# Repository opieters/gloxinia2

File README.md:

# gloxinia2

This is the second version of [Gloxinia](https://github.com/opieters/gloxinia), a research-focussed measurement platform that is tailored for deployment in greenhouses. Its goals are simple interconnectivity, flexbibility and cost-effectiveness.

## Architecture

The general architecture from the inital version remained, but some boards are not separate noted in place of add-on components. At it's core, the system comprises of a set of communicating nodes. Three possible options are:
- dicio: a node with serial interconnectivity, such that the system can interface with a computer. This node also features storage (16GB). This node can also send commands to other nodes in case of errors or crashes.
- sylvatica: a node with eight 16-bit ADCs
- planalta: a node with four LIAs (advanced analogue sensors)

All nodes communicate over a CAN bus and dicio nodes also have UART connection for communication computers. Plugging in a USB-C cable in the right port should suffice to connect to the system. Make sure to only plug cables to matching interfaces, since the hardware can be damaged otherwise. The interfaces are detailed in the PCB design and the interface section below. 

Note that the CAN bus requires termination. No automatic termination is implemented, so the use needs to manually terminate the CAN lines!

Each board interface also has an I2C port (not that some of the ports share the same physical interface), and analogue ports and a One Wire port. One Wire is currently not supported in the software. 

## Interfacing

Each node consists of a stack of boards. The base board with the analogue and digital processing, a botton connectivity board to interconnect different nodes and an optional top interfacing board (only for sylvatica).

### Dicio

Base board: [IF1] [IF2] [IF3] [IF4]
IF board: [Serial/USB] [] [CAN] [CAN]

### Sylvatica

Top board: [IF4] [IF5] [IF6] [IF7]
Base board: [IF1] [IF2] [IF3] [IF4]
IF board: [] [] [CAN] [CAN]

### Planalta

Base board: [IF1] [IF2] [IF3] [IF4]
IF board: [] [] [CAN] [CAN]

Note that IF1-4 are not feature-identical, IF1 supports a faster LIA (when others disabled) than IF2, 3 and 4 resp. See software implementation for details. These interfaces to no feature a 1W port.

## Software

The software consists of several parts: the embedded C code, the C++ GUI and the Python readout script. 

The embedded code is in the `firmware` folder. A separate MPLAB X project is created per hardware board (dicio, planalta and sylvatica). The code is written in C and compiled with the XC16 compiler. The code is written in a modular fashion, such that it is easy to add new features. The code is documented in the source files. Common files are included in the `lib2` folder. 

A bootloader project was also created to update the devices over CAN and UART, but this was not tested and should not yet be used in production. The UART version was slightly tested and first results were promising.

The GUI code is written in C++ using the Qt framework. A recent version of Qt 6 is necessary to build the project. Qt Designer files are included with in the `gui_qt` folder to get started with this project. 

## Enclousure

A 3D printable enclosure design is included in the `enclosure` folder, along with the STL files. The design is made in OpenSCAD.

A radiation shield was also designed for the environemental sensors, which is included in the

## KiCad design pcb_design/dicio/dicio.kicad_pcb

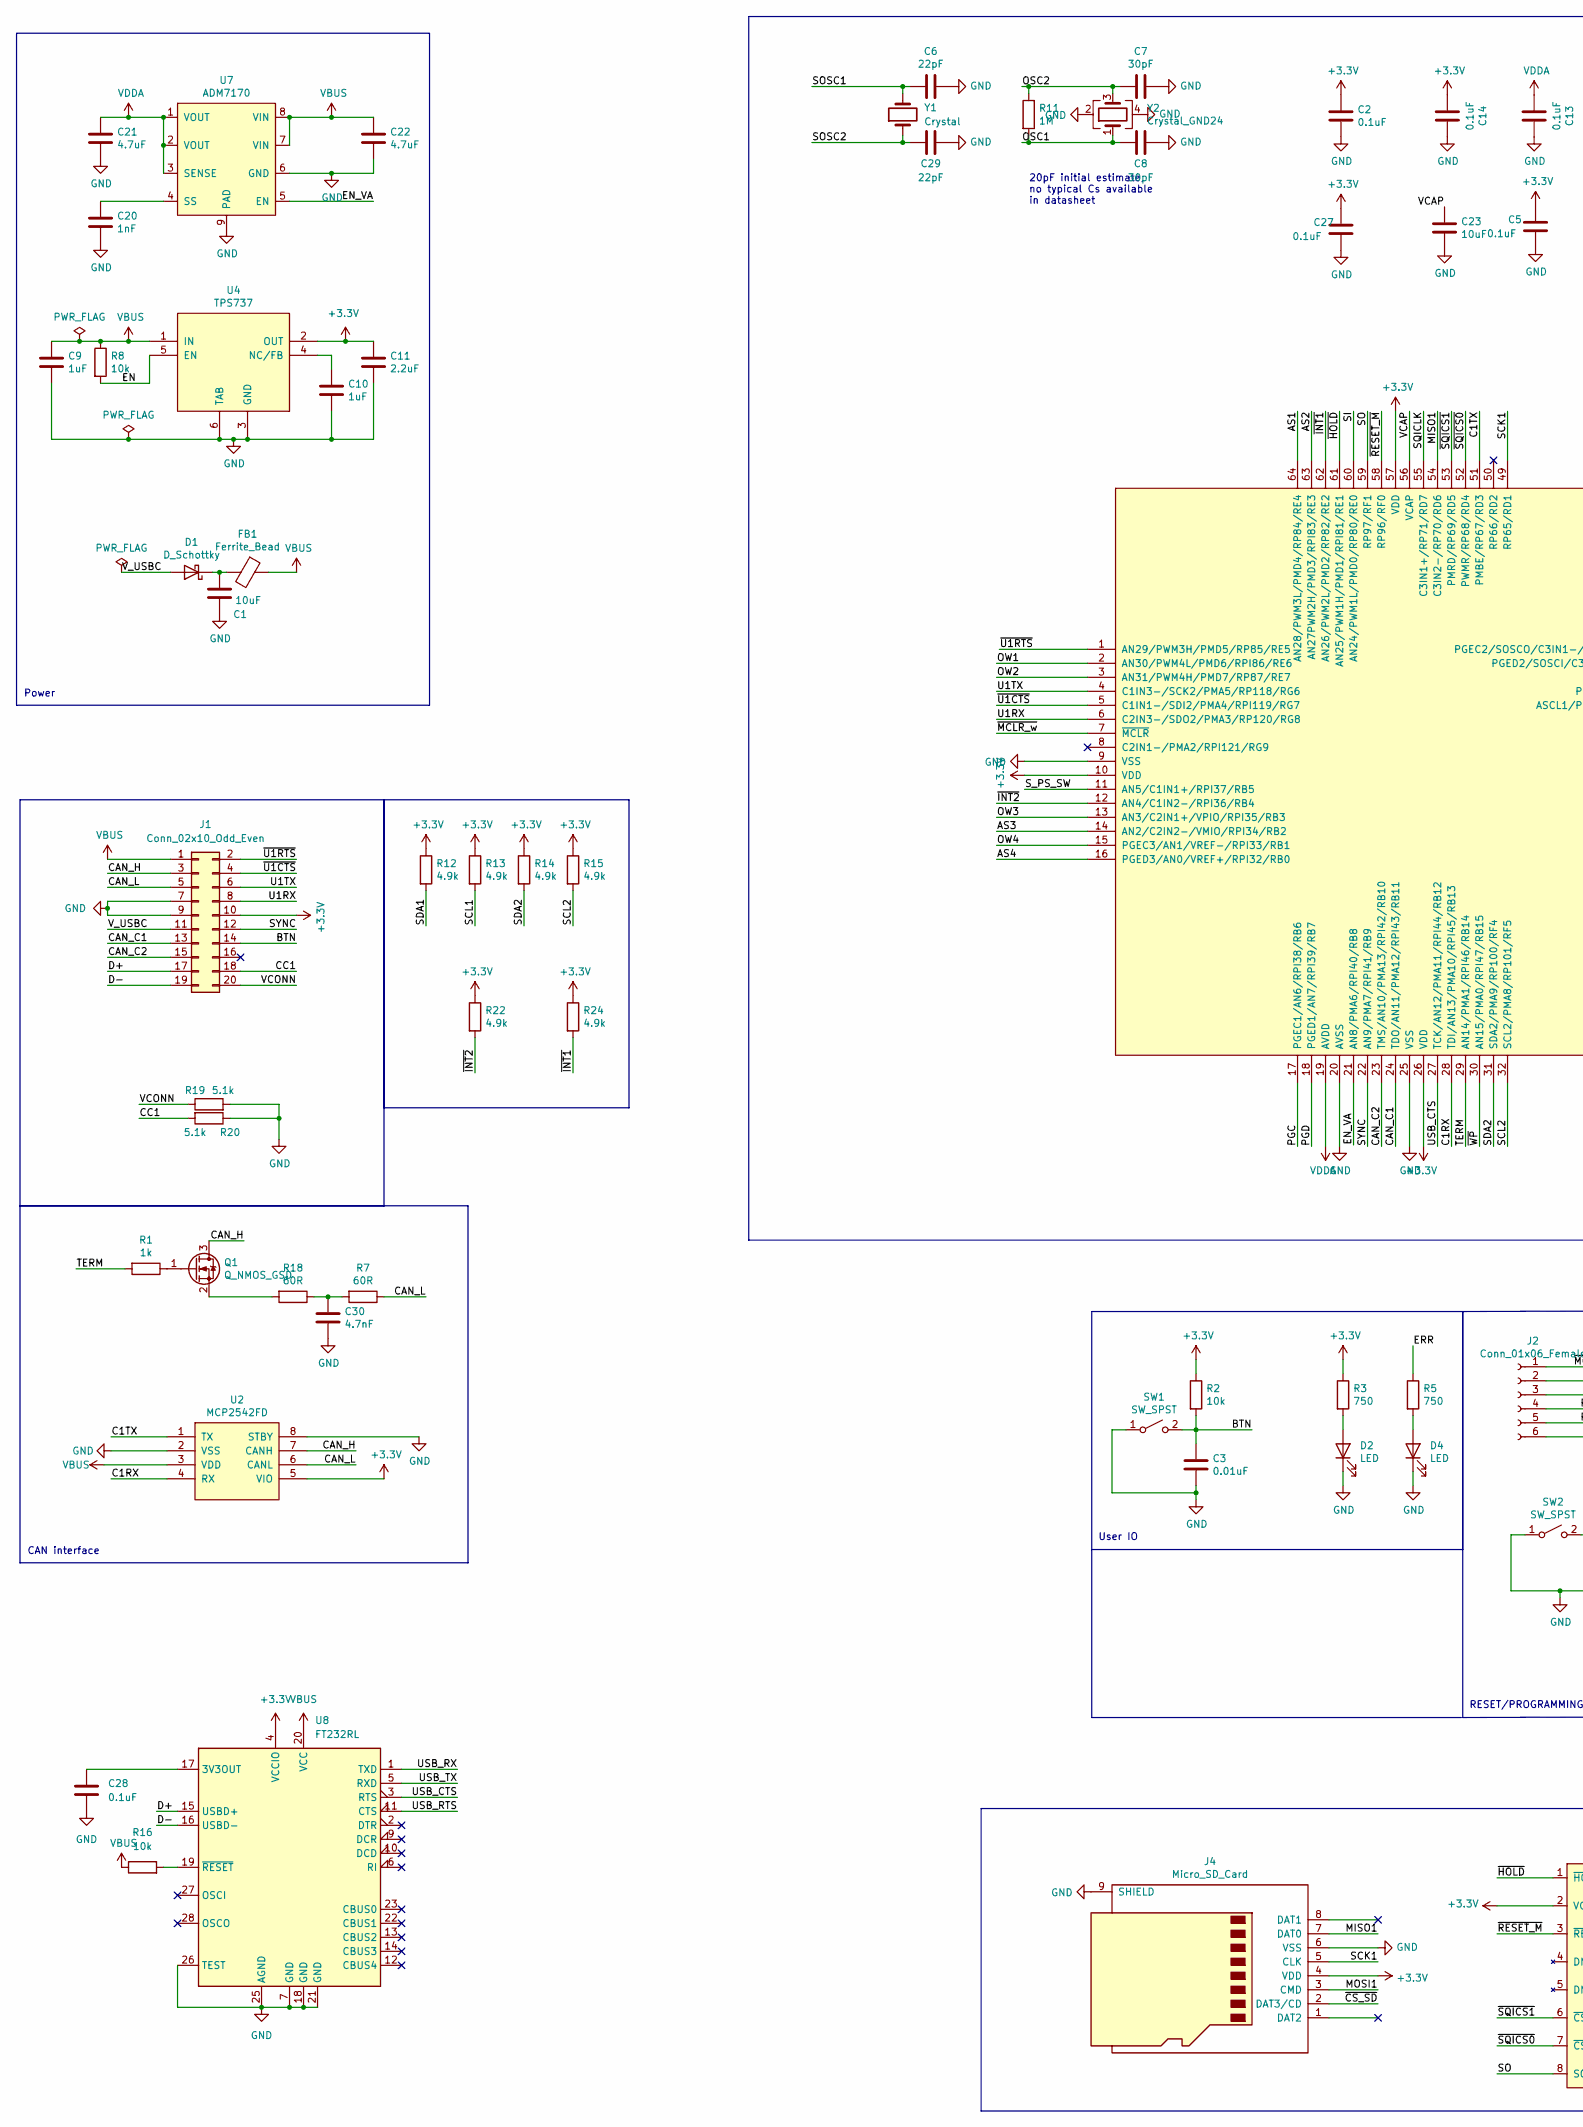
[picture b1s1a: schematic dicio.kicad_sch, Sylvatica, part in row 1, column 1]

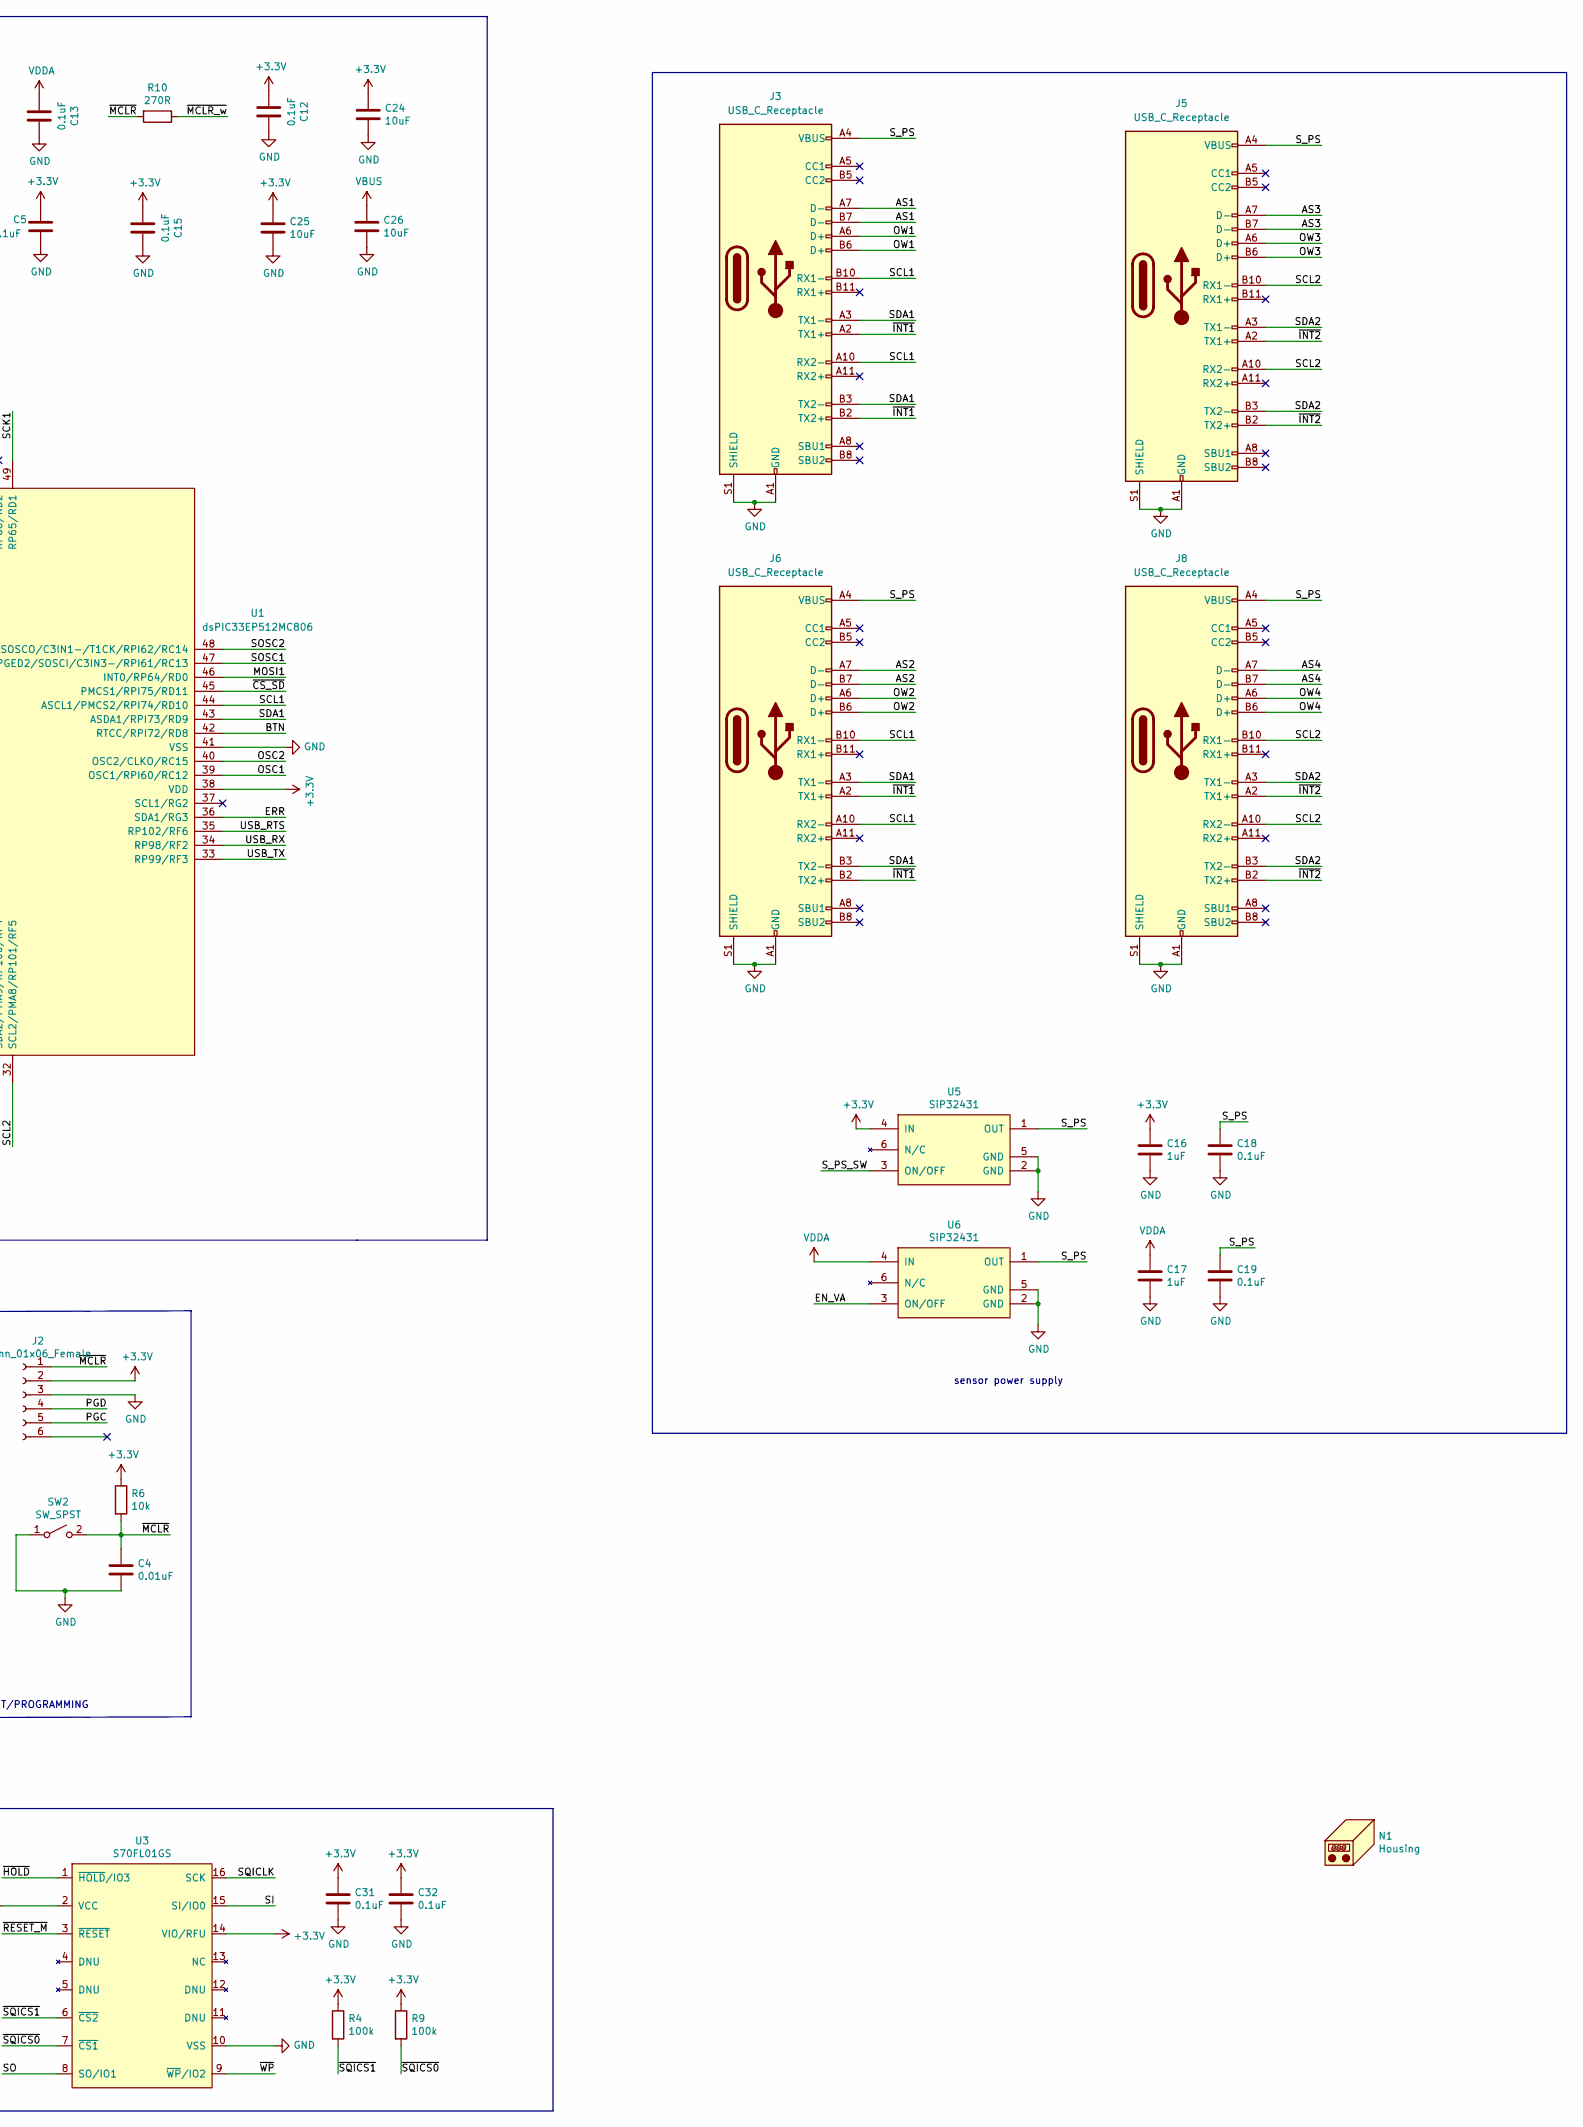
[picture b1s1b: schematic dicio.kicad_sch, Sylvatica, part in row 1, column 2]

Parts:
C1, C24, C25, C26: 10uF; C_1210_3225Metric; Mouser 963-TMK325BJ106KM-P
C2, C5, C12, C13, C14, C15, C27: 0.1uF; C_0603_1608Metric; Mouser 710-885012206071
C3, C4: 0.01uF; C_0603_1608Metric; Mouser 710-885012206065
C6, C29: 22pF; C_0603_1608Metric; Mouser 80-C0603C220J3HACTU
C7, C8: 30pF; C_0603_1608Metric; Mouser 80-C0603C300G1HACTU
C9, C10: 1uF; C_0603_1608Metric; Mouser 963-TMK325B7105KD-T
C11: 2.2uF; C_1206_3216Metric; Mouser 791-1206X225K250CT
C16, C17: 1uF; C_0603_1608Metric
C18, C19, C28, C31, C32: 0.1uF; C_0603_1608Metric
C20: 1nF; C_0603_1608Metric
C21, C22: 4.7uF; C_1206_3216Metric; Mouser 80-C1206C475K4PAC
C23: 10uF; C_1210_3225Metric
C30: 4.7nF; C_0603_1608Metric
D1: D_Schottky; D_SMB; Mouser 621-B340LB-F
D2, D4: LED; LED_0603_1608Metric; Mouser 78-TLMS1000
FB1: Ferrite_Bead; L_0805_2012Metric; Mouser 875-MI0805K400R-10
J1: Conn_02x10_Odd_Even; SAMTEC_TMMH-110-01-T-DV
J2: Conn_01x06_Female; PinSocket_1x06_P2.54mm_Vertical
J3, J5, J6, J8: USB_C_Receptacle; USB_C_Receptacle_Amphenol_12401861XX12A; Mouser 523-124018612112A
J4: Micro_SD_Card; microSD_HC_Wuerth_693072010801
N1: Housing; Enclosure-Gloxinia4; Mouser 546-1554LA2GYCL
Q1: Q_NMOS_GSD; SOT-23; Mouser 771-PMV20XNER
R1: 1k; R_0603_1608Metric
R2, R6, R8: 10k; R_0603_1608Metric; Mouser 284-APC0603B10K0N
R3, R5: 750; R_0603_1608Metric; Mouser 603-RC0603FR-07750RL
R4, R9: 100k; R_0603_1608Metric
R7, R18: 60R; R_0603_1608Metric; Mouser 594-5063JD120R0F
R10: 270R; R_0603_1608Metric; Mouser 603-RC0603FR-07270RL
R11: 1M; R_0603_1608Metric
R12, R13, R14, R15, R22, R24: 4.9k; R_0603_1608Metric; Mouser 603-RC0603FR-0724K9L
R16: 10k; R_0603_1608Metric
R19, R20: 5.1k; R_0603_1608Metric; Mouser 603-AC0603FR-135K1L
SW1, SW2: SW_SPST; SW_Push_1P1T_NO_CK_KMR2; Mouser 611-KMR621NGLFS
U1: dsPIC33EP512MC806; TQFP-64_10x10mm_P0.5mm
U2: MCP2542FD; SOIC-8_3.9x4.9mm_P1.27mm; Mouser 579-MCP2542FDT-E/SN
U3: S70FL01GS; SOIC-16_25.75x18.75mm_P2.5mm
U4: TPS737; SOT-223-6; Mouser 595-TPS73733DCQR
U5, U6: SiP32431; SOT-363_SC-70-6
U7: ADM7170; LFCSP-8-1EP_3x3mm_P0.5mm_EP1.45x1.74mm
U8: FT232RL; SSOP-28_5.3x10.2mm_P0.65mm
Y1: Crystal; Crystal_SMD_3215-2Pin_3.2x1.5mm; Mouser 520-.327-9-34QCNT
Y2: Crystal_GND24; Crystal_SMD_Abracon_ABM3B-4Pin_5.0x3.2mm; Mouser 520-80-10-30B-CWNT

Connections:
+3.3V: C2.1, C5.1, C11.1, C12.2, C14.2, C15.1, C16.1, C24.1, C25.1, C27.1, C31.1, C32.1, J1.10, J2.2, J4.4 (VDD), R2.1, R3.1, R4.1, R6.1, R9.1, R12.1, R13.1, R14.1, R15.1, R22.1, R24.1, U1.10 (VDD), U1.26 (VDD), U1.38 (VDD), U1.57 (VDD), U2.5 (VIO), U3.2 (VCC), U3.14 (VIO/RFU), U4.2 (OUT), U5.4 (IN), U8.4 (VCCIO)
/AS1: J3.A7 (D-), J3.B7 (D-), U1.64 (AN28/PWM3L/PMD4/RP84/RE4)
/AS2: J6.A7 (D-), J6.B7 (D-), U1.63 (AN27PWM2H/PMD3/RPI83/RE3)
/AS3: J5.A7 (D-), J5.B7 (D-), U1.14 (AN2/C2IN2-/VMIO/RPI34/RB2)
/AS4: J8.A7 (D-), J8.B7 (D-), U1.16 (PGED3/AN0/VREF+/RPI32/RB0)
/BTN: C3.1, J1.14, R2.2, SW1.2 (B), U1.42 (RTCC/RPI72/RD8)
/C1RX: U1.28 (TDI/AN13/PMA10/RPI45/RB13), U2.4 (RX)
/C1TX: U1.51 (PMBE/RP67/RD3), U2.1 (TX)
/CAN_C1: J1.13, U1.24 (TDO/AN11/PMA12/RPI43/RB11)
/CAN_C2: J1.15, U1.23 (TMS/AN10/PMA13/RPI42/RB10)
/CAN_H: J1.3, Q1.3 (D), U2.7 (CANH)
/CAN_L: J1.5, R7.1, U2.6 (CANL)
/CC1: J1.18, R20.2
/D+: J1.17, U8.15 (USBD+)
/D-: J1.19, U8.16 (USBD-)
/EN: R8.2, U4.5 (EN)
/EN_VA: U1.21 (AN8/PMA6/RPI40/RB8), U6.3 (ON/OFF), U7.5 (EN)
/ERR: R5.1, U1.36 (SDA1/RG3)
/MISO1: J4.7 (DAT0), U1.54 (C3IN2-/RP70/RD6)
/MOSI1: J4.3 (CMD), U1.46 (INT0/RP64/RD0)
/OSC1: C8.2, R11.2, U1.39 (OSC1/RPI60/RC12), Y2.1
/OSC2: C7.2, R11.1, U1.40 (OSC2/CLKO/RC15), Y2.3
/OW1: J3.A6 (D+), J3.B6 (D+), U1.2 (AN30/PWM4L/PMD6/RPI86/RE6)
/OW2: J6.A6 (D+), J6.B6 (D+), U1.3 (AN31/PWM4H/PMD7/RP87/RE7)
/OW3: J5.A6 (D+), J5.B6 (D+), U1.13 (AN3/C2IN1+/VPIO/RPI35/RB3)
/OW4: J8.A6 (D+), J8.B6 (D+), U1.15 (PGEC3/AN1/VREF-/RPI33/RB1)
/PGC: J2.5, U1.17 (PGEC1/AN6/RPI38/RB6)
/PGD: J2.4, U1.18 (PGED1/AN7/RPI39/RB7)
/SCK1: J4.5 (CLK), U1.49 (RP65/RD1)
/SCL1: J3.A10 (RX2-), J3.B10 (RX1-), J6.A10 (RX2-), J6.B10 (RX1-), R13.2, U1.44 (ASCL1/PMCS2/RPI74/RD10)
/SCL2: J5.A10 (RX2-), J5.B10 (RX1-), J8.A10 (RX2-), J8.B10 (RX1-), R15.2, U1.32 (SCL2/PMA8/RP101/RF5)
/SDA1: J3.A3 (TX1-), J3.B3 (TX2-), J6.A3 (TX1-), J6.B3 (TX2-), R12.2, U1.43 (ASDA1/RPI73/RD9)
/SDA2: J5.A3 (TX1-), J5.B3 (TX2-), J8.A3 (TX1-), J8.B3 (TX2-), R14.2, U1.31 (SDA2/PMA9/RP100/RF4)
/SI: U1.60 (AN24/PWM1L/PMD0/RP80/RE0), U3.15 (SI/IO0)
/SO: U1.59 (RP97/RF1), U3.8 (SO/IO1)
/SOSC1: C6.2, U1.47 (PGED2/SOSCI/C3IN3-/RPI61/RC13), Y1.2
/SOSC2: C29.2, U1.48 (PGEC2/SOSCO/C3IN1-/T1CK/RPI62/RC14), Y1.1
/SQICLK: U1.55 (C3IN1+/RP71/RD7), U3.16 (SCK)
/SYNC: J1.12, U1.22 (AN9/PMA7/RPI41/RB9)
/S_PS: C18.1, C19.1, J3.A4 (VBUS), J3.A9 (VBUS), J3.B4 (VBUS), J3.B9 (VBUS), J5.A4 (VBUS), J5.A9 (VBUS), J5.B4 (VBUS), J5.B9 (VBUS), J6.A4 (VBUS), J6.A9 (VBUS), J6.B4 (VBUS), J6.B9 (VBUS), J8.A4 (VBUS), J8.A9 (VBUS), J8.B4 (VBUS), J8.B9 (VBUS), U5.1 (OUT), U6.1 (OUT)
/S_PS_SW: U1.11 (AN5/C1IN1+/RPI37/RB5), U5.3 (ON/OFF)
/TERM: R1.2, U1.29 (AN14/PMA1/RPI46/RB14)
/U1RX: J1.8, U1.6 (C2IN3-/SDO2/PMA3/RP120/RG8)
/U1TX: J1.6, U1.4 (C1IN3-/SCK2/PMA5/RP118/RG6)
/USB_CTS: U1.27 (TCK/AN12/PMA11/RPI44/RB12), U8.3 (RTS)
/USB_RTS: U1.35 (RP102/RF6), U8.11 (CTS)
/USB_RX: U1.34 (RP98/RF2), U8.1 (TXD)
/USB_TX: U1.33 (RP99/RF3), U8.5 (RXD)
/VCAP: C23.1, U1.56 (VCAP)
/VCONN: J1.20, R19.1
/V_USBC: D1.2 (A), J1.11
/~CS_SD: J4.2 (DAT3/CD), U1.45 (PMCS1/RPI75/RD11)
/~HOLD: U1.61 (AN25/PWM1H/PMD1/RPI81/RE1), U3.1 (~HOLD/IO3)
/~INT1: J3.A2 (TX1+), J3.B2 (TX2+), J6.A2 (TX1+), J6.B2 (TX2+), R24.2, U1.62 (AN26/PWM2L/PMD2/RP82/RE2)
/~INT2: J5.A2 (TX1+), J5.B2 (TX2+), J8.A2 (TX1+), J8.B2 (TX2+), R22.2, U1.12 (AN4/C1IN2-/RPI36/RB4)
/~MCLR_w: R10.1, U1.7 (~MCLR)
/~MCLR: C4.1, J2.1, R6.2, R10.2, SW2.2 (B)
/~RESET_M: U1.58 (RP96/RF0), U3.3 (~RESET)
/~SQICS0: R9.2, U1.52 (PWMR/RP68/RD4), U3.7 (~CS1)
/~SQICS1: R4.2, U1.53 (PMRD/RP69/RD5), U3.6 (~CS2)
/~U1CTS: J1.4, U1.5 (C1IN1-/SDI2/PMA4/RPI119/RG7)
/~U1RTS: J1.2, U1.1 (AN29/PWM3H/PMD5/RP85/RE5)
/~WP: U1.30 (AN15/PMA0/RPI47/RB15), U3.9 (~WP/IO2)
GND: C1.2, C2.2, C3.2, C4.2, C5.2, C6.1, C7.1, C8.1, C9.2, C10.2, C11.2, C12.1, C13.1, C14.1, C15.2, C16.2, C17.2, C18.2, C19.2, C20.2, C21.2, C22.2, C23.2, C24.2, C25.2, C26.2, C27.2, C28.2, C29.1, C30.2, C31.2, C32.2, D2.1 (K), D4.1 (K), J1.7, J1.9, J2.3, J3.A1 (GND), J3.A12 (GND), J3.B1 (GND), J3.B12 (GND), J3.S1 (SHIELD), J4.6 (VSS), J4.9 (SHIELD), J5.A1 (GND), J5.A12 (GND), J5.B1 (GND), J5.B12 (GND), J5.S1 (SHIELD), J6.A1 (GND), J6.A12 (GND), J6.B1 (GND), J6.B12 (GND), J6.S1 (SHIELD), J8.A1 (GND), J8.A12 (GND), J8.B1 (GND), J8.B12 (GND), J8.S1 (SHIELD), R19.2, R20.1, SW1.1 (A), SW2.1 (A), U1.9 (VSS), U1.20 (AVSS), U1.25 (VSS), U1.41 (VSS), U2.2 (VSS), U2.8 (STBY), U3.10 (VSS), U4.3 (GND), U4.6 (TAB), U5.2 (GND), U5.5 (GND), U6.2 (GND), U6.5 (GND), U7.6 (GND), U7.9 (PAD), U8.7 (GND), U8.18 (GND), U8.21 (GND), U8.25 (AGND), U8.26 (TEST), Y2.2, Y2.4
unnamed: C1.1, D1.1 (K), FB1.2
unnamed: C10.1, U4.4 (NC/FB)
unnamed: C20.1, U7.4 (SS)
unnamed: C28.1, U8.17 (3V3OUT)
unnamed: C30.1, R7.2, R18.1
unnamed: D2.2 (A), R3.2
unnamed: D4.2 (A), R5.2
unnamed: Q1.1 (G), R1.1
unnamed: Q1.2 (S), R18.2
unnamed: R16.2, U8.19 (~RESET)
VBUS: C9.1, C22.1, C26.1, FB1.1, J1.1, R8.1, R16.1, U2.3 (VDD), U4.1 (IN), U7.7 (VIN), U7.8 (VIN), U8.20 (VCC)
VDDA: C13.2, C17.1, C21.1, U1.19 (AVDD), U6.4 (IN), U7.1 (VOUT), U7.2 (VOUT), U7.3 (SENSE)

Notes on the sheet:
sensor power supply
20pF initial estimate, no typical Cs available in datasheet
RESET/PROGRAMMING
CAN interface
User IO
Power

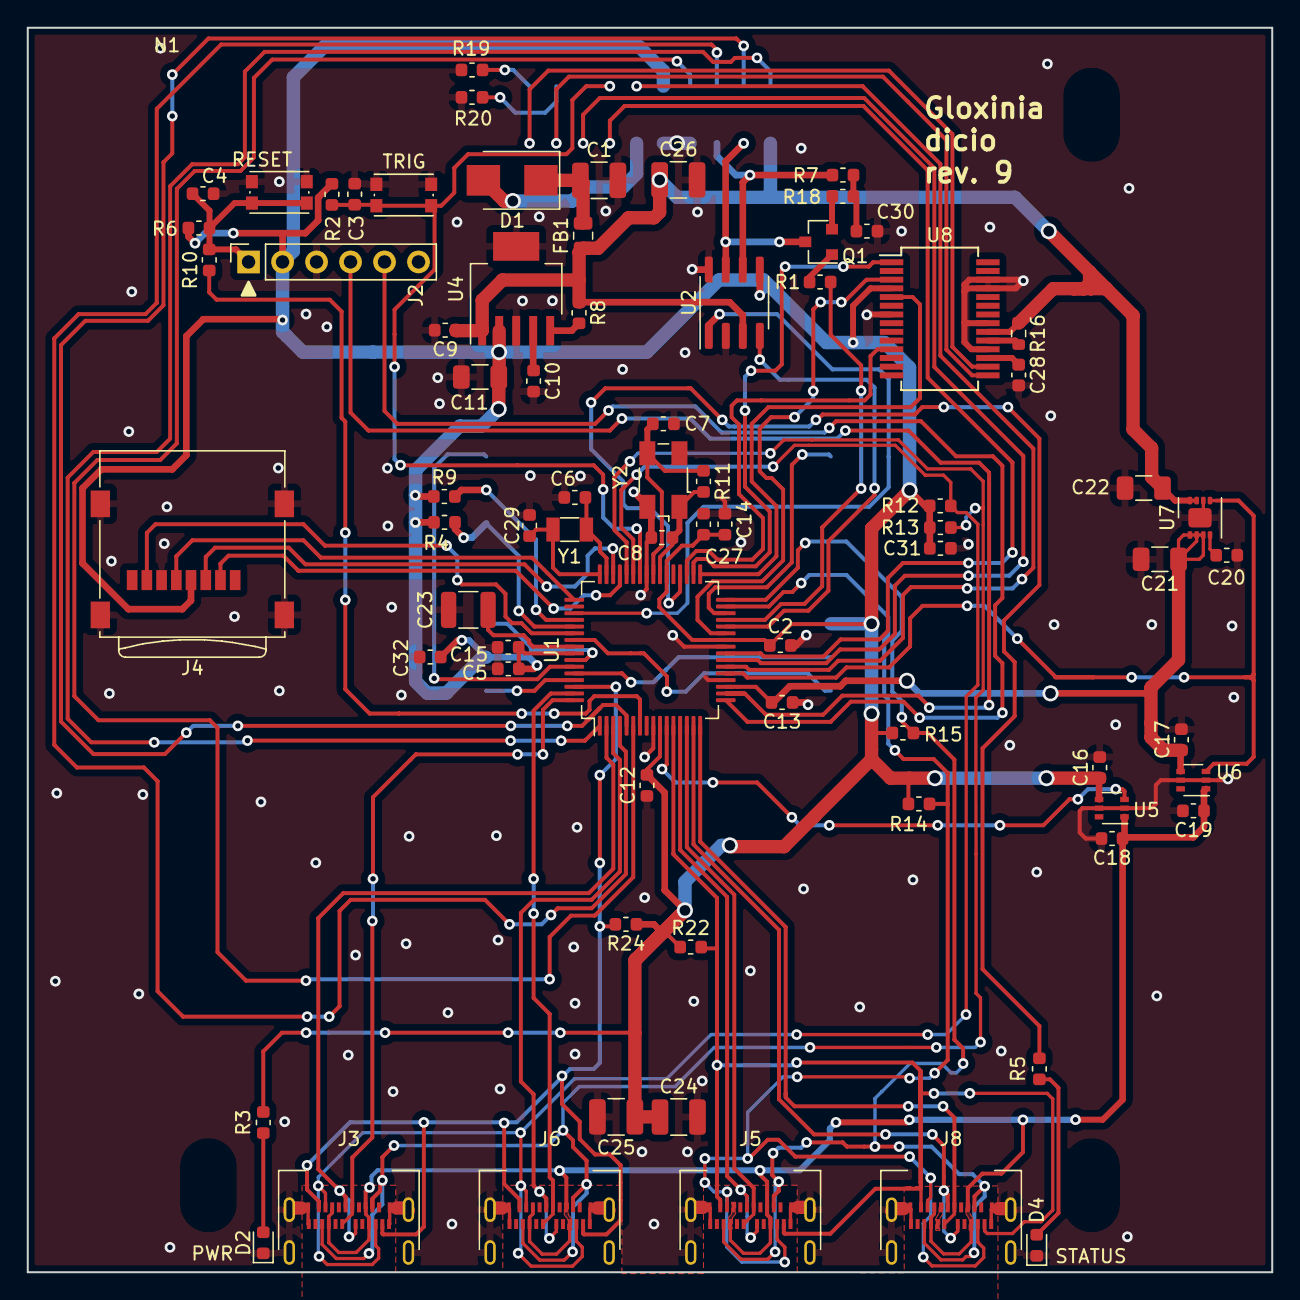
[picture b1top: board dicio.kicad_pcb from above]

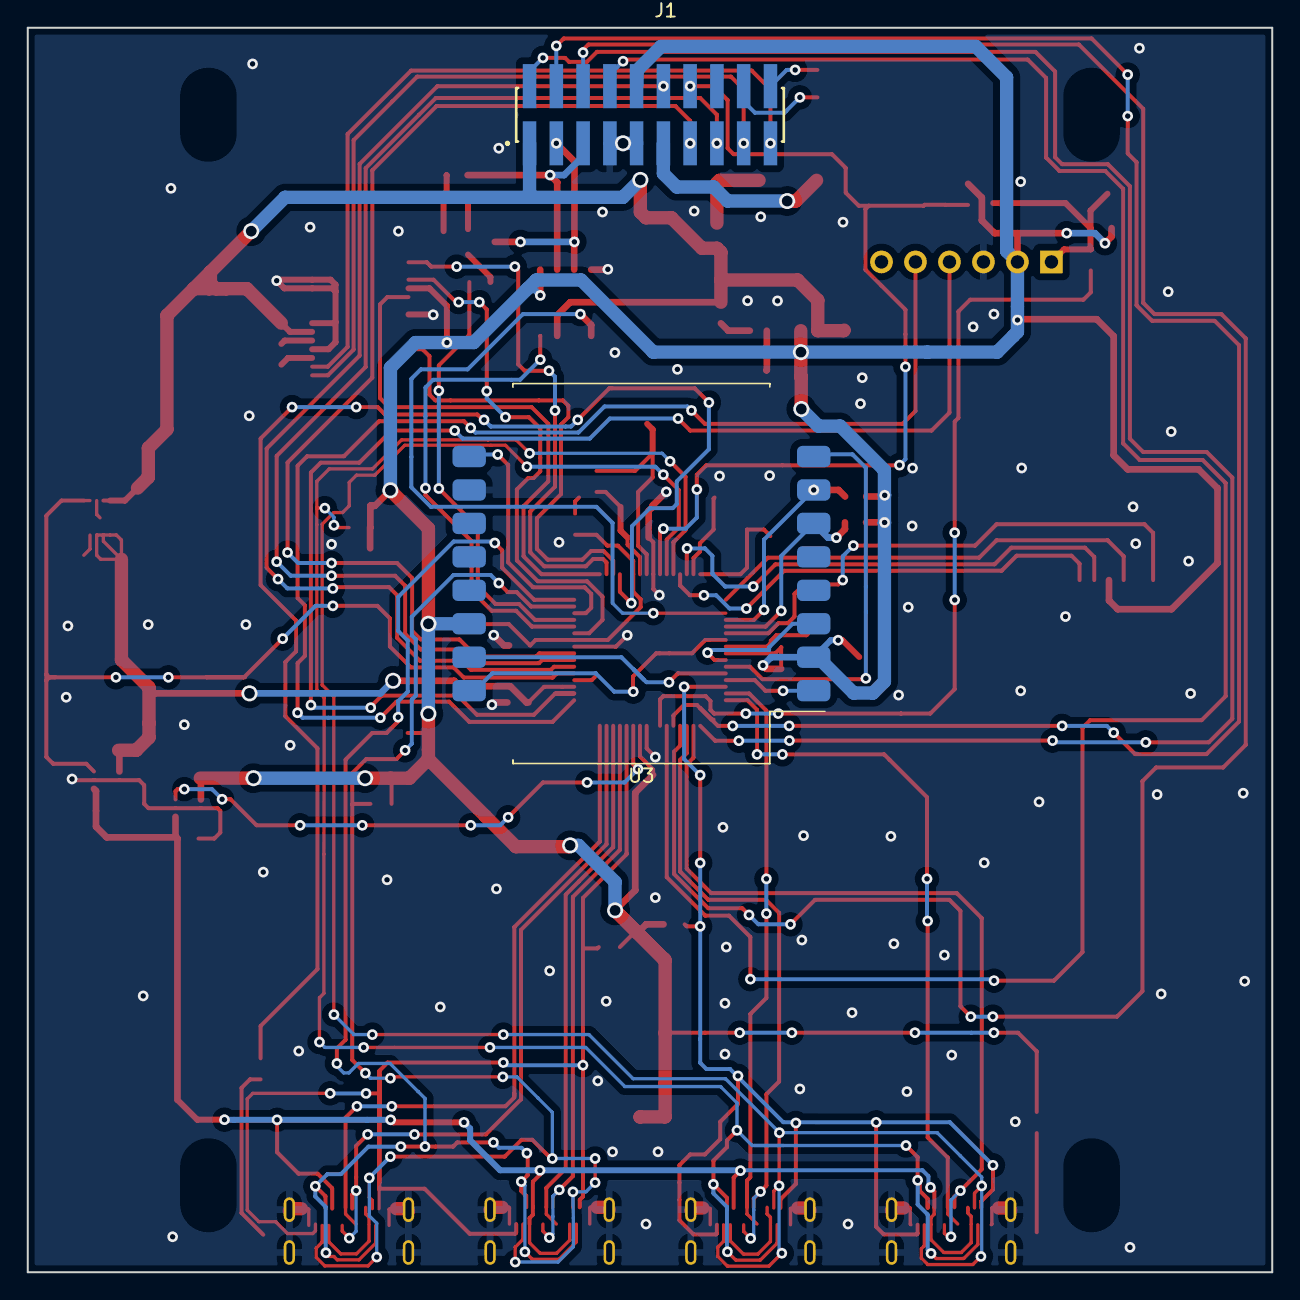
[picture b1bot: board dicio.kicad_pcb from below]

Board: 2 copper layers, 93.0 x 93.0 mm, 78 parts (2 on the bottom side), 76 nets.

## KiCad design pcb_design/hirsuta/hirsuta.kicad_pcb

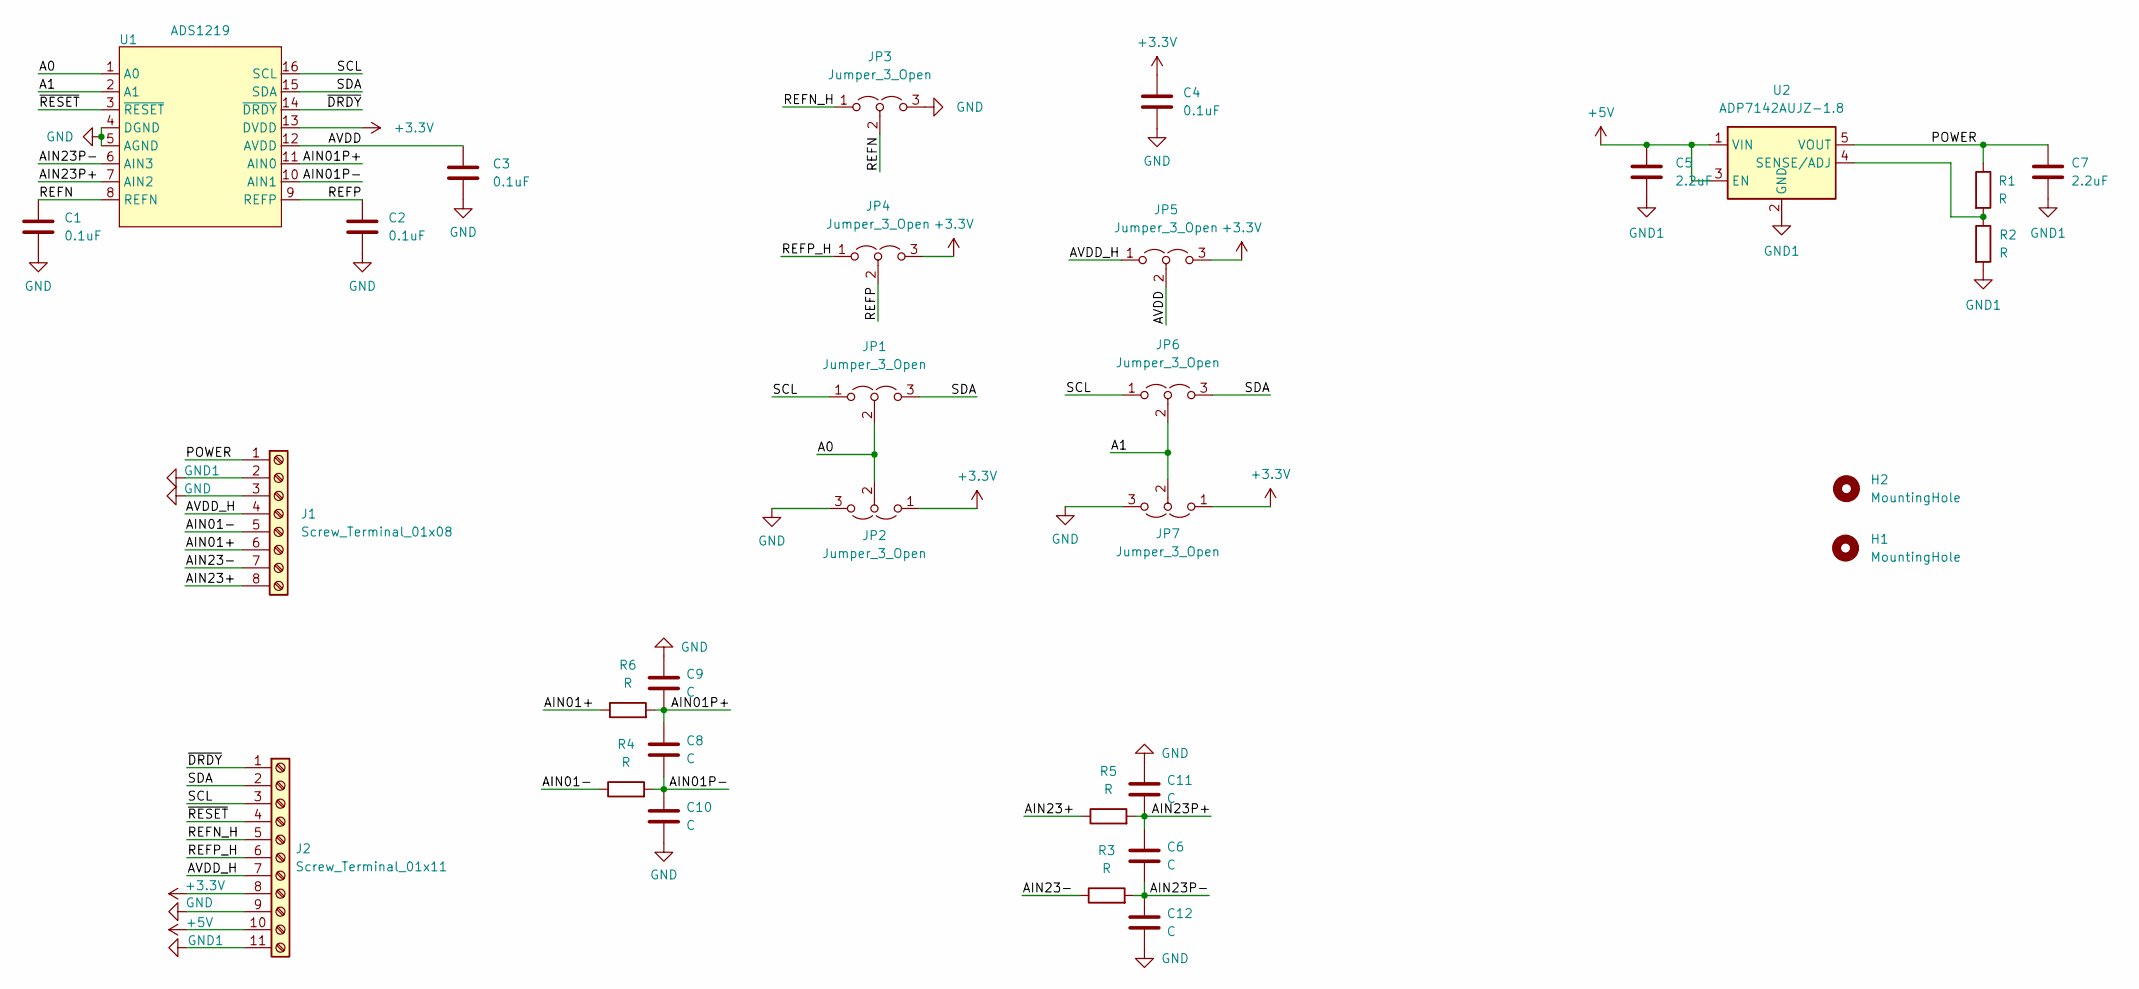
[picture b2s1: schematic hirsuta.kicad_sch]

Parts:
C1, C2, C3, C4: 0.1uF; C_0603_1608Metric
C5, C7: 2.2uF; C_1206_3216Metric
C6, C8, C9, C10, C11, C12: C; C_0603_1608Metric
H1, H2: MountingHole; MountingHole_3.2mm_M3
J1: Screw_Terminal_01x08; TerminalBlock_Phoenix_PT-1,5-8-3.5-H_1x08_P3.50mm_Horizontal
J2: Screw_Terminal_01x11; TerminalBlock_Phoenix_PT-1,5-11-3.5-H_1x11_P3.50mm_Horizont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
JP1, JP2, JP3, JP4, JP5, JP6, JP7: Jumper_3_Open; SolderJumper-3_P1.3mm_Open_Pad1.0x1.5mm
R1, R2, R3, R4, R5, R6: R; C_0603_1608Metric
U1: ADS1219; TSSOP-16-1EP_4.4x5mm_P0.65mm
U2: ADP7142AUJZ-1.8; TSOT-23-5

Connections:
+3.3V: C4.1, J2.8, JP2.1 (A), JP4.3 (B), JP5.3 (B), JP7.1 (A), U1.13 (DVDD)
+5V: C5.1, J2.10, U2.1 (VIN), U2.3 (EN)
/A0: JP1.2 (C), JP2.2 (C), U1.1 (A0)
/A1: JP6.2 (C), JP7.2 (C), U1.2 (A1)
/AIN01+: J1.6, R6.1
/AIN01-: J1.5, R4.1
/AIN01P+: C8.1, C9.2, R6.2, U1.11 (AIN0)
/AIN01P-: C8.2, C10.1, R4.2, U1.10 (AIN1)
/AIN23+: J1.8, R5.1
/AIN23-: J1.7, R3.1
/AIN23P+: C6.1, C11.2, R5.2, U1.7 (AIN2)
/AIN23P-: C6.2, C12.1, R3.2, U1.6 (AIN3)
/AVDD: C3.1, JP5.2 (C), U1.12 (AVDD)
/AVDD_H: J1.4, J2.7, JP5.1 (A)
/POWER: C7.1, J1.1, R1.1, U2.5 (VOUT)
/REFN: C1.1, JP3.2 (C), U1.8 (REFN)
/REFN_H: J2.5, JP3.1 (A)
/REFP: C2.1, JP4.2 (C), U1.9 (REFP)
/REFP_H: J2.6, JP4.1 (A)
/SCL: J2.3, JP1.1 (A), JP6.1 (A), U1.16 (SCL)
/SDA: J2.2, JP1.3 (B), JP6.3 (B), U1.15 (SDA)
/~DRDY: J2.1, U1.14 (~DRDY)
/~RESET: J2.4, U1.3 (~RESET)
GND: C1.2, C2.2, C3.2, C4.2, C9.1, C10.2, C11.1, C12.2, J1.3, J2.9, JP2.3 (B), JP3.3 (B), JP7.3 (B), U1.4 (DGND), U1.5 (AGND)
GND1: C5.2, C7.2, J1.2, J2.11, R2.2, U2.2 (GND)
unnamed: R1.2, R2.1, U2.4 (SENSE/ADJ)

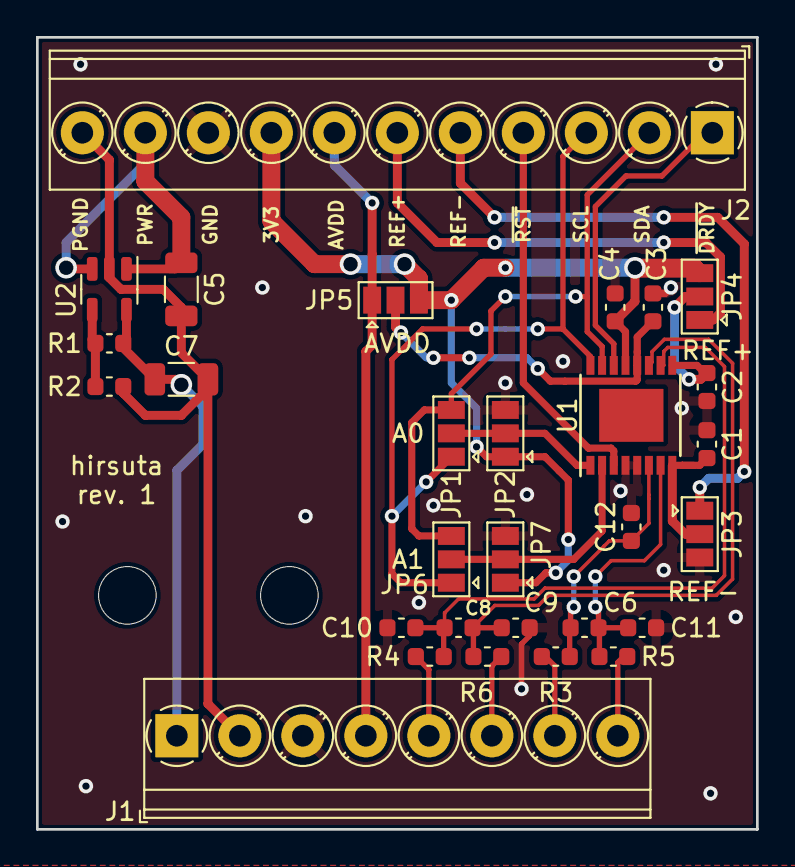
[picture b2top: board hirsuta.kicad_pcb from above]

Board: 2 copper layers, 40.0 x 44.0 mm, 31 parts (0 on the bottom side), 26 nets.

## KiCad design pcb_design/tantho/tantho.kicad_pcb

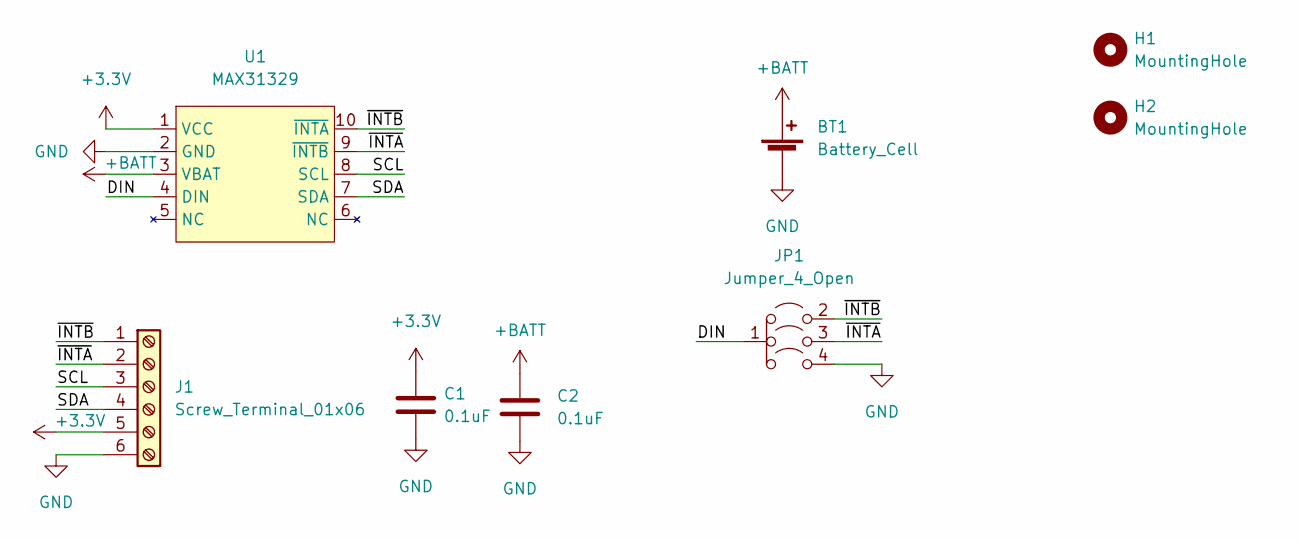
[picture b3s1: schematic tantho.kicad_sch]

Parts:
BT1: Battery_Cell; SMTM1225
C1, C2: 0.1uF; C_0603_1608Metric
H1, H2: MountingHole; MountingHole_3.2mm_M3
J1: Screw_Terminal_01x06; TerminalBlock_Phoenix_PT-1,5-6-3.5-H_1x06_P3.50mm_Horizontal
JP1: Jumper_4_Open; SolderJumper-4_Open_Pad1.0x1.5mm
U1: MAX31329; LGA10_5x5mm_21-100481

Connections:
+3.3V: C1.1, J1.5, U1.1 (VCC)
+BATT: BT1.1 (+), C2.1, U1.3 (VBAT)
/DIN: JP1.1 (A), U1.4 (DIN)
/SCL: J1.3, U1.8 (SCL)
/SDA: J1.4, U1.7 (SDA)
/~INTA: J1.2, JP1.3 (B), U1.9 (~INTB)
/~INTB: J1.1, JP1.2 (B), U1.10 (~INTA)
GND: BT1.2 (-), C1.2, C2.2, J1.6, JP1.4 (B), U1.2 (GND)

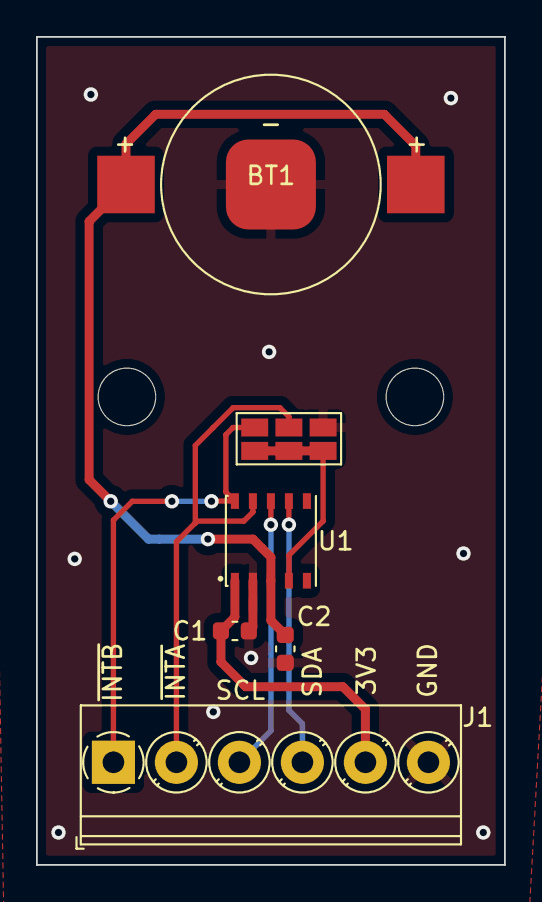
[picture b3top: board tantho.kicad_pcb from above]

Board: 2 copper layers, 26.0 x 46.0 mm, 8 parts (0 on the bottom side), 8 nets.
